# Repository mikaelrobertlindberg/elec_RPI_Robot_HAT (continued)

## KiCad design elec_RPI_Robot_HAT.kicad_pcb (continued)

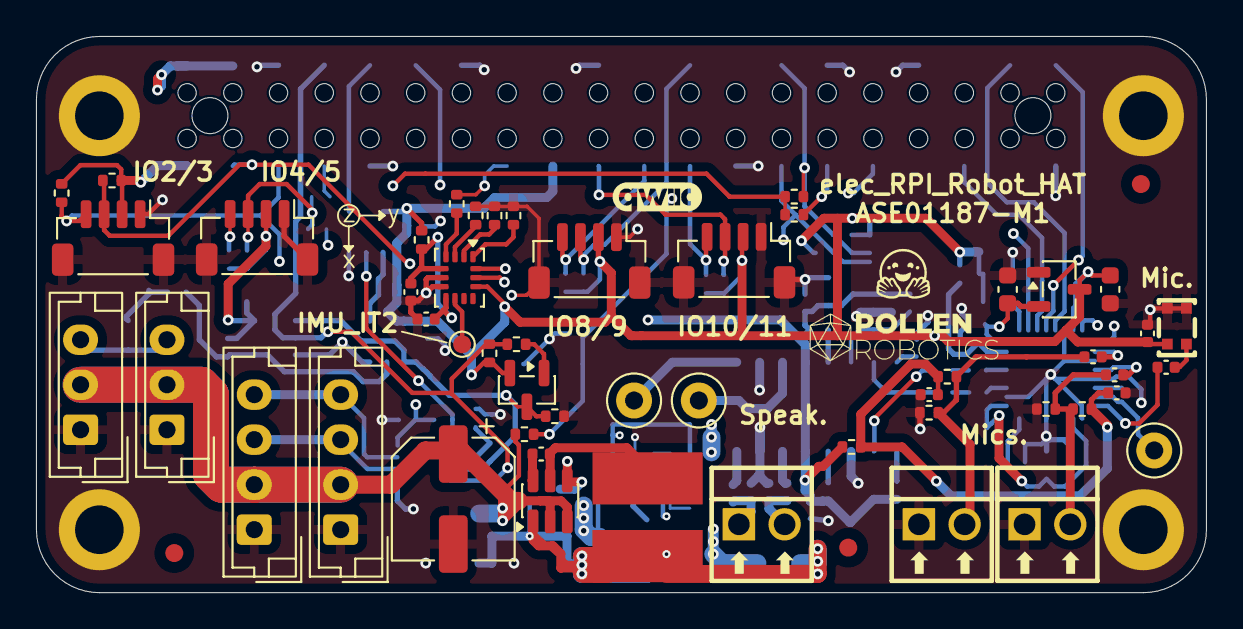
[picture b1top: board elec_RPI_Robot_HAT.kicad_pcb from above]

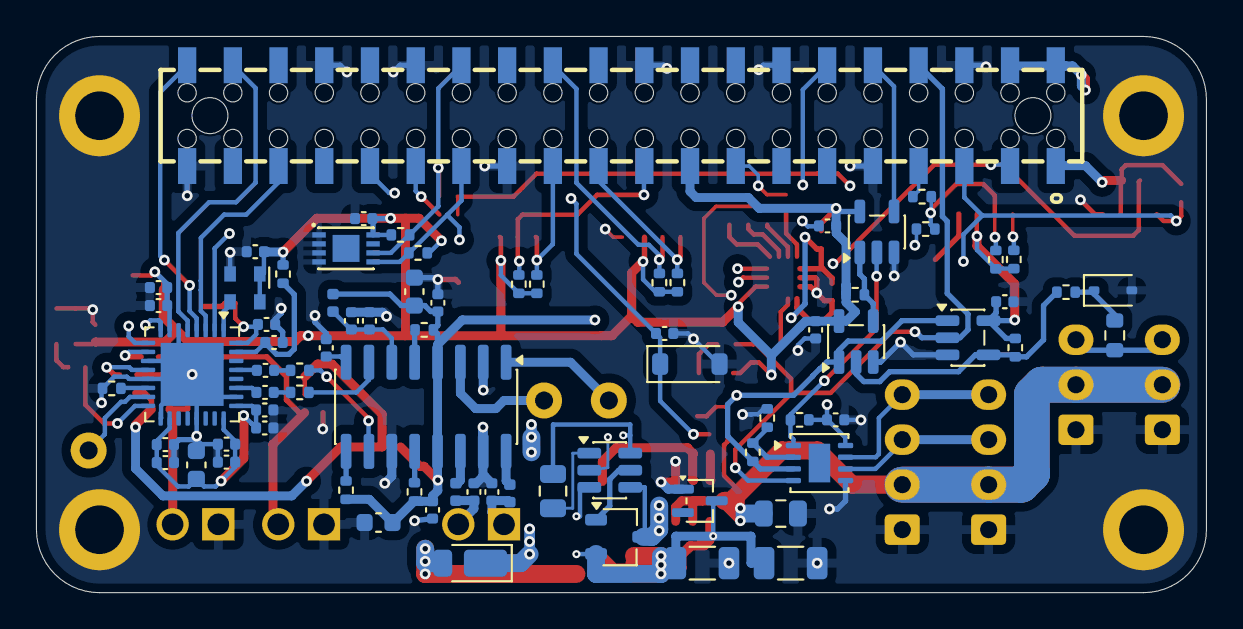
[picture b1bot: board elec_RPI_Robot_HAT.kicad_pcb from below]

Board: 4 copper layers, 65.0 x 30.9 mm, 132 parts (75 on the bottom side), 74 nets.

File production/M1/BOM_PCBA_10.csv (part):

Item,Designators,Quantity per board,Quantity for 10 boards,Manufacturer,Manufacturer Part Number,Value,Footprint,LCSC Part Number,Source,Source URL,Stock checked,Observed stock,Populate
1,"C1, C2, C3, C4, C6, C10, C27, C29, C31, C33, C35, C40, C41, C42, C43",15,150,SAMSUNG(三星),CL05A105KA5NQNC,1u,RobotHAT:C_0402_1005Metric_C1 / RobotHAT:C_0402_1005Metric_C10 / RobotHAT:C_0402_1005Metric_C2 / RobotHAT:C_0402_1005Metric_C27 / RobotHAT:C_0402_1005Metric_C29 / RobotHAT:C_0402_1005Metric_C3 / RobotHAT:C_0402_1005Metric_C31 / RobotHAT:C_0402_1005Metric_C33 / RobotHAT:C_0402_1005Metric_C35 / RobotHAT:C_0402_1005Metric_C4 / RobotHAT:C_0402_1005Metric_C40 / RobotHAT:C_0402_1005Metric_C41 / RobotHAT:C_0402_1005Metric_C42 / RobotHAT:C_0402_1005Metric_C43 / RobotHAT:C_0402_1005Metric_C6,C52923,LCSC,https://www.lcsc.com/product-detail/C52923.html,2026-11-09,2908400,YES
2,"C5, C7, C12, C13, C37",5,50,SAMSUNG(三星),CL10A106MQ8NNNC,10u,RobotHAT:C_0603_1608Metric_C12 / RobotHAT:C_0603_1608Metric_C13 / RobotHAT:C_0603_1608Metric_C37 / RobotHAT:C_0603_1608Metric_C5 / RobotHAT:C_0603_1608Metric_C7,C1691,LCSC,https://www.lcsc.com/product-detail/C1691.html,2026-11-09,491910,YES
3,"C8, C9",2,20,muRata(村田),GRM1555C1H221JA01D,220p 50V C0G,RobotHAT:C_0402_1005Metric_C8 / RobotHAT:C_0402_1005Metric_C9,C71693,LCSC,https://www.lcsc.com/product-detail/C71693.html,2026-11-09,1193500,YES
4,"C11, C14, C15, C16, C17, C18, C20, C26, C28, C30, C32, C36, C38",13,130,SAMSUNG(三星),CL05B104KB54PNC,100n / 100n 50V,RobotHAT:C_0402_1005Metric_C11 / RobotHAT:C_0402_1005Metric_C14 / RobotHAT:C_0402_1005Metric_C15 / RobotHAT:C_0402_1005Metric_C16 / RobotHAT:C_0402_1005Metric_C17 / RobotHAT:C_0402_1005Metric_C18 / RobotHAT:C_0402_1005Metric_C20 / RobotHAT:C_0402_1005Metric_C26 / RobotHAT:C_0402_1005Metric_C28 / RobotHAT:C_0402_1005Metric_C30 / RobotHAT:C_0402_1005Metric_C32 / RobotHAT:C_0402_1005Metric_C36 / RobotHAT:C_0402_1005Metric_C38,C307331,LCSC,https://www.lcsc.com/product-detail/C307331.html,2026-11-09,2506000,YES
5,C19,1,10,Panasonic,EEE-FK1J100P,10u 63V,RobotHAT:Panasonic_FK_D_6.3x5.8_C19,,DigiKey,https://www.digikey.se/en/products/detail/panasonic-industry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,2026-11-09,14595,YES
6,"C21, C22",2,20,Murata,GRM31CR61C476ME44L,47u 16V,RobotHAT:C_1206_C21 / RobotHAT:C_1206_C22,C385047,LCSC,https://www.lcsc.com/product-detail/C385047.html,2026-11-09,1833,YES
7,"C23, C24",2,20,SAMSUNG(三星),CL05B104KO5NNNC,100n 16V,RobotHAT:C_0402_1005Metric_C23 / RobotHAT:C_0402_1005Metric_C24,C1525,LCSC,https://www.lcsc.com/product-detail/C1525.html,2026-11-09,3026000,YES
8,"C34, C44",2,20,SAMSUNG(三星),CL05B103KB5NNNC,10n,RobotHAT:C_0402_1005Metric_C34 / RobotHAT:C_0402_1005Metric_C44,C15195,LCSC,https://www.lcsc.com/product-detail/C15195.html,2026-11-09,968700,YES
9,C39,1,10,Murata,GRM21BR71H224KA01L,220n 50V,RobotHAT:C_0805_C39,C86042,LCSC,https://www.lcsc.com/product-detail/C86042.html,2026-11-09,6175,YES
10,C45,1,10,Chinocera(华瓷),HGC0805R5106K350NSLJ,10u 35V,RobotHAT:C_0805_2012Metric_C45,C33546007,LCSC,https://www.lcsc.com/product-detail/C33546007.html,2026-11-09,379510,YES
11,D1,1,10,onsemi,BAT54WT1G,BAT54W,RobotHAT:SOT-323_SC-70_D1,,DigiKey,https://www.digikey.se/en/products/detail/onsemi/BAT54WT1G/918320,2026-11-09,429,YES
12,D2,1,10,R+O(宏嘉诚),BZT52B3V3,3V3 Zener Diode,RobotHAT:D_SOD-123_D2,C19077392,LCSC,https://www.lcsc.com/product-detail/C19077392.html,2026-11-09,270940,YES
13,D4,1,10,DIODES(美台),BZT52C5V1S-7-F,5V1,RobotHAT:D_SOD-323_D4,C151348,LCSC,https://www.lcsc.com/product-detail/C151348.html,2026-11-09,56280,YES
14,D5,1,10,Diodes Incorporated,SBR3U40P1-7,SBR3U40P1-7,RobotHAT:D_PowerDI123_D5,C97127,LCSC,https://www.lcsc.com/product-detail/C97127.html,2026-11-09,9655,YES
15,FB1,1,10,muRata(村田),BLM15AG601SN1D,0.3A 600R@100MHz,RobotHAT:L_0402_1005Metric_FB1,C76884,LCSC,https://www.lcsc.com/product-detail/C76884.html,2026-11-09,748800,YES
16,"FB2, FB3",2,20,muRata(村田),BLM15PX121SN1D,2A - 120R@100MHz,RobotHAT:L_0402_1005Metric_FB2 / RobotHAT:L_0402_1005Metric_FB3,C88970,DigiKey,https://www.digikey.se/en/products/detail/murata-electronics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,2026-11-09,173030,YES
17,"J1, J2, J9",3,30,DORABO(地博电气),DB125-2.54-2P-GN-S,Screw term.,RobotHAT:CONN-TH_DB125-2.54-2P-GN_J1 / RobotHAT:CONN-TH_DB125-2.54-2P-GN_J2 / RobotHAT:CONN-TH_DB125-2.54-2P-GN_J9,C918120,LCSC,https://www.lcsc.com/product-detail/C918120.html,2026-11-09,28940,YES
18,"J3, J11",2,20,JST,B4B-EH-A(LF)(SN),Dynamixel-4,RobotHAT:JST_EH_B4B-EH-A_1x04_P2.50mm_Vertical_J11 / RobotHAT:JST_EH_B4B-EH-A_1x04_P2.50mm_Vertical_J3,C160258,LCSC,https://www.lcsc.com/product-detail/C160258.html,2026-11-09,42240,YES
19,J4,1,10,Liansheng(连盛),FH-00339,Female Header 2x20 SMD,RobotHAT:PinHeader_2x20_P2.54mm_Vertical_with_rasp_HAT_zero_SMD_connector_J4,C2685112,LCSC,https://www.lcsc.com/product-detail/C2685112.html,2026-11-09,8387,YES
20,"J5, J6, J7, J8",4,40,JST,BM04B-SRSS-TB(LF)(SN),JST SH,RobotHAT:JST_SH_BM04B-SRSS-TB_1x04-1MP_P1.00mm_Vertical_J5 / RobotHAT:JST_SH_BM04B-SRSS-TB_1x04-1MP_P1.00mm_Vertical_J6 / RobotHAT:JST_SH_BM04B-SRSS-TB_1x04-1MP_P1.00mm_Vertical_J7 / RobotHAT:JST_SH_BM04B-SRSS-TB_1x04-1MP_P1.00mm_Vertical_J8,C160390,LCSC,https://www.lcsc.com/product-detail/C160390.html,2026-11-09,1645,YES
21,"J13, J14",2,20,JST,B3B-EH-A(LF)(SN),Dynamixel-3,RobotHAT:JST_EH_B3B-EH-A_1x03_P2.50mm_Vertical_J13 / RobotHAT:JST_EH_B3B-EH-A_1x03_P2.50mm_Vertical_J14,C160259,LCSC,https://www.lcsc.com/product-detail/C160259.html,2026-11-09,73430,YES
22,L4,1,10,Eaton,SDCHA1V6045-4R7-R,4u7 4.5A,RobotHAT:Eaton_SDCHA1V6045_L4,,DigiKey,https://www.digikey.se/en/products/detail/eaton-electronics-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,2026-11-09,4455,YES
23,MK1,1,10,LinkMems(聆麦声学),LMA2718T421-OA5-2,Microphone_MEMS,RobotHAT:MIC-SMD_4P-L2.8-W1.9-P1.84-TL_MK1,C7587901,LCSC,https://www.lcsc.com/product-detail/C7587901.html,2026-11-09,9870,YES
24,Q1,1,10,TWGMC(迪嘉),MMBT3906,MMBT3906,RobotHAT:SOT-23_Q1,C727128,LCSC,https://www.lcsc.com/product-detail/C727128.html,2026-11-09,313450,YES
25,Q2,1,10,Diodes Incorporated,DMN3023L-7,DMN3023L-7,RobotHAT:TSOT-23_Q2,C443825,LCSC,https://www.lcsc.com/product-detail/C443825.html,2026-11-09,7645,YES
26,"R1, R2, R6, R12, R13, R20, R21, R24, R26, R27, R29, R31, R32, R34, R35, R38, R39",17,170,UNI-ROYAL(厚声),0402WGF1002TCE,10k,RobotHAT:R_0402_1005Metric_R1 / RobotHAT:R_0402_1005Metric_R12 / RobotHAT:R_0402_1005Metric_R13 / RobotHAT:R_0402_1005Metric_R2 / RobotHAT:R_0402_1005Metric_R20 / RobotHAT:R_0402_1005Metric_R21 / RobotHAT:R_0402_1005Metric_R24 / RobotHAT:R_0402_1005Metric_R26 / RobotHAT:R_0402_1005Metric_R27 / RobotHAT:R_0402_1005Metric_R29 / RobotHAT:R_0402_1005Metric_R31 / RobotHAT:R_0402_1005Metric_R32 / RobotHAT:R_0402_1005Metric_R34 / RobotHAT:R_0402_1005Metric_R35 / RobotHAT:R_0402_1005Metric_R38 / RobotHAT:R_0402_1005Metric_R39 / RobotHAT:R_0402_1005Metric_R6,C25744,LCSC,https://www.lcsc.com/product-detail/C25744.html,2026-11-09,1442800,YES
27,"R3, R4, R5, R7, R9, R14, R15, R18, R19, R25, R30, R40",12,120,UNI-ROYAL(厚声),0402WGF0000TCE,0R,RobotHAT:R_0402_1005Metric_R14 / RobotHAT:R_0402_1005Metric_R15 / RobotHAT:R_0402_1005Metric_R18 / RobotHAT:R_0402_1005Metric_R19 / RobotHAT:R_0402_1005Metric_R25 / RobotHAT:R_0402_1005Metric_R3 / RobotHAT:R_0402_1005Metric_R30 / RobotHAT:R_0402_1005Metric_R4 / RobotHAT:R_0402_1005Metric_R40 / RobotHAT:R_0402_1005Metric_R5 / RobotHAT:R_0402_1005Metric_R7 / RobotHAT:R_0402_1005Metric_R9,C17168,LCSC,https://www.lcsc.com/product-detail/C17168.html,2026-11-09,8561100,YES
28,"R22, R23",2,20,YAGEO(国巨),RC0402FR-074K7L,4k7,RobotHAT:R_0402_1005Metric_R22 / RobotHAT:R_0402_1005Metric_R23,C105871,LCSC,https://www.lcsc.com/product-detail/C105871.html,2026-11-09,11573800,YES
29,R28,1,10,UNI-ROYAL(厚声),0402WGF2002TCE,20k,RobotHAT:R_0402_1005Metric_R28,C25765,LCSC,https://www.lcsc.com/product-detail/C25765.html,2026-11-09,699600,YES
30,R33,1,10,FOJAN(富捷),FRC0402F1500TS,150R,RobotHAT:R_0402_1005Metric_R33,C2909321,LCSC,https://www.lcsc.com/product-detail/C2909321.html,2026-11-09,867900,YES
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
